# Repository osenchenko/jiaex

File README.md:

#  JiaEX - split keyboard for extended alphabets.

`assembled-keyboard.stl` - 3d model of assembled keyboard.

## Features

- enough keys for placing on base layer all letters for extended alphabets (alphabets with more than 26 letters).
- plenty of keys for playing with different variants to find your best setup.
- one keyboard for all operating systems. Switch between settings for different operating systems with a shortcut (currently settings for Linux and Windows are implemented).
- used AT90USB1286 with 128 KB memory. No limits for storing settings.
- wide choice of keycaps. The keyboard is designed for maximum use of keycap sets from standard keyboards. 1.75U keys of thumb cluster and 1.5U vertical keys can be replaced with 1.5U or 1.25U keys in any combination.
- wrist pad is rigidly attached to the keyboard. The keyboard is not intended to be used without a wrist pad.
- the display shows current default layout (for example Linux) and current active layer plus Caps Lock state.
- powered by QMK.

## Layout

[keyboard-layout-editor.com](http://www.keyboard-layout-editor.com/#/gists/80bbde035c246cb868fec8fd4ef6ad40)

## Build guide

### Folders

- `case` - stl-files for 3d printing case and wrist pads. <br/>Case and wrist pads are designed by Alexander_St enginemojo@gmail.com.
- `datasheets` - datasheets for some used parts
- `firmware` - source files for QMK firmware
- `pcb` - KiCAD source and gerber files for manufacturing PCB.
- `plate` - dxf for laser cutting metal plate.

### Firmware

- install qmk 
- copy folder `jiaex` from `firmware` to `keyboards` folder of qmk installation
- <u>Until pull request [#11487](https://github.com/qmk/qmk_firmware/pull/11487) is not merged in QMK master you must apply this pull request by yourself.</u>
- run `qmk flash -kb jiaex -km default` 

### PCB and Case

Kicad libraries used:

- https://github.com/XenGi/teensy_library

### Bill of materials

| Name                                          | Value                                                                                                            | Quantity |
| --------------------------------------------- | ---------------------------------------------------------------------------------------------------------------- | -------: |
| Microcontroller board                         | [Teensy ++ 2.0](https://www.pjrc.com/store/teensypp.html)                                                        |        2 |
| SMD Diode                                     | 1N4148 [SOD-123]                                                                                                 |       68 |
| SMD Resistor 1206                             | 30K                                                                                                              |        2 |
| SMD Resistor 1206                             | 3K                                                                                                               |        4 |
| SMD Resistor 1206                             | 10K                                                                                                              |        1 |
| Jack RJ-22                                    | [215875-1, Conn RJ-22 F 4 POS 1.02mm Solder RA Thru-Hole 4 Terminal 1 Port Cat 3 T/R](datasheets/Jack_RJ-22.pdf) |        2 |
| OLED display                                  | [0.91 inch OLED Module 128x32, I2C](datasheets/OLED_Module_User_Manual_EN.pdf)                                   |        1 |
| Plug for OLED display                         | [PLS-4R (DS1022-1x4R)](datasheets/DS1022.pdf)                                                                    |        1 |
| Key switch                                    | Any Cherry MX compatible                                                                                         |       68 |
| Key stabilyzers                               | Any Cherry MX compatible, plate mount                                                                            |        6 |
| 4-wire phone cable with RJ11 (TP-4P4C) jacks. | Max length of cable - 11 cm.                                                                                     |        1 |
| Rubber feet                                   | At your own choice. I use [RF-3004](datasheets/DOC004505728.pdf)                                                 |      --- |
| Metal plate. Thickness                        | 1.5 mm                                                                                                           |        2 |

### Screws

| Name                                                                                                   | Diameter, mm | Length, mm | Image               | Quantity | Notes                                                   |
| ------------------------------------------------------------------------------------------------------ | -----------: | ---------: | ------------------- | -------: | ------------------------------------------------------- |
| Self-tapping screw for plastic, countersunk head, blunt end, Phillips head, full thread, ART 9090      |            3 |      8..10 |  |       20 | Drill the hole with a 2 mm drill before insert screw.   |
| Self-tapping screw DIN 7981 FH (A2) with a blunt end with a half-cylindrical head, head Phillips ST2.2 |          2.2 |     6.5..8 |  |        8 | Drill the hole with a 1.2 mm drill before insert screw. |

## Inspiration

Keyboard is inspired by the following keyboards:

- Jian
- Jiran
- Ultimate Hacking Keyboard
- Ergodox

Layout inspired by ideas of:

- Tonsky https://tonsky.livejournal.com/318571.html (for non-Russian speakers use google translate  in Chrome browser)
- Ultimate Hacking Keyboard
- Optozorax https://github.com/optozorax/moonlander (for non-Russian speakers use google translate in Chrome browser)

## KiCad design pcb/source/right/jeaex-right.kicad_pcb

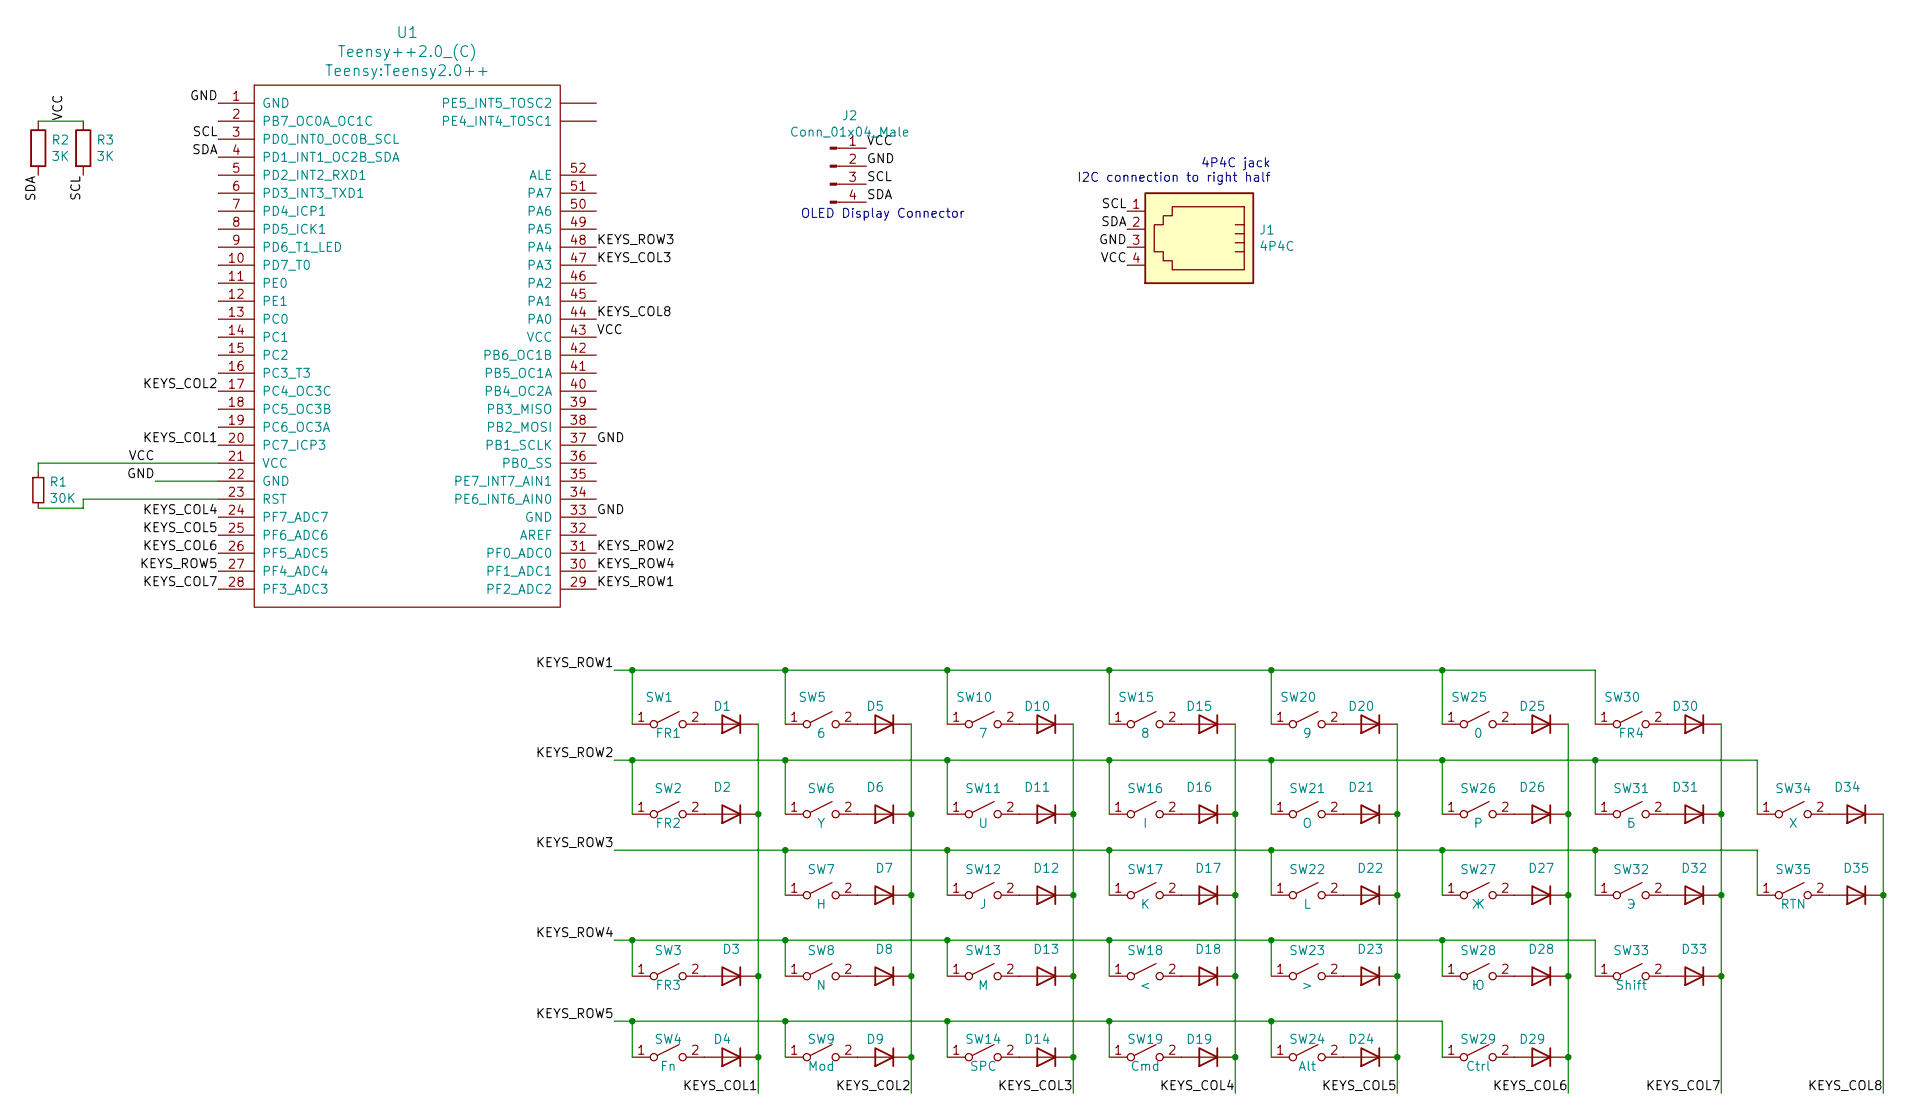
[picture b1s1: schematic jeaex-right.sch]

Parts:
D1, D2, D3, D4, D5, D6, D7, D8, D9, D10, D11, D12, D13, D14, D15, D16, D17, D18, D19, D20, D21, D22, D23, D24, D25, D26, D27, D28, D29, D30, D31, D32, D33, D34, D35: 1N4148W; D_SOD-123
J1: 4P4C; 4P4C_Jack_0955012441
J2: Conn_01x04_Male; PinHeader_1x04_P2.54mm_Vertical
R1: 30K; R_1206_3216Metric_Pad1.30x1.75mm_HandSolder
R2, R3: 3K; R_1206_3216Metric_Pad1.30x1.75mm_HandSolder
SW1: FR1; SW_Cherry_MX_1.00u_Plate
SW2: FR2; SW_Cherry_MX_1.50u_Plate
SW3: FR3; SW_Cherry_MX_1.50u_Plate
SW4: Fn; SW_Cherry_MX_1.75u_Plate
SW5: 6; SW_Cherry_MX_1.00u_Plate
SW6: Y; SW_Cherry_MX_1.00u_Plate
SW7: H; SW_Cherry_MX_1.00u_Plate
SW8: N; SW_Cherry_MX_1.00u_Plate
SW9: Mod; SW_Cherry_MX_1.75u_Plate
SW10: 7; SW_Cherry_MX_1.00u_Plate
SW11: U; SW_Cherry_MX_1.00u_Plate
SW12: J; SW_Cherry_MX_1.00u_Plate
SW13: M; SW_Cherry_MX_1.00u_Plate
SW14: SPC; SW_Cherry_MX_1.75u_Plate
SW15: 8; SW_Cherry_MX_1.00u_Plate
SW16: I; SW_Cherry_MX_1.00u_Plate
SW17: K; SW_Cherry_MX_1.00u_Plate
SW18: <; SW_Cherry_MX_1.00u_Plate
SW19: Cmd; SW_Cherry_MX_1.25u_Plate
SW20: 9; SW_Cherry_MX_1.00u_Plate
SW21: O; SW_Cherry_MX_1.00u_Plate
SW22: L; SW_Cherry_MX_1.00u_Plate
SW23: >; SW_Cherry_MX_1.00u_Plate
SW24: Alt; SW_Cherry_MX_1.25u_Plate
SW25: 0; SW_Cherry_MX_1.00u_Plate
SW26: P; SW_Cherry_MX_1.00u_Plate
SW27: Ж; SW_Cherry_MX_1.00u_Plate
SW28: Ю; SW_Cherry_MX_1.00u_Plate
SW29: Ctrl; SW_Cherry_MX_2.25u_Plate
SW30: FR4; SW_Cherry_MX_2.00u_Plate
SW31: Б; SW_Cherry_MX_1.00u_Plate
SW32: Э; SW_Cherry_MX_1.00u_Plate
SW33: Shift; SW_Cherry_MX_2.75u_Plate
SW34: Х; SW_Cherry_MX_1.00u_Plate
SW35: RTN; SW_Cherry_MX_2.25u_Plate
U1: Teensy++2.0_(C); Teensy2.0++

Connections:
/GND: J1.3, J2.2, U1.1 (GND), U1.22 (GND), U1.33 (GND), U1.37 (PB1_SCLK)
/KEYS_COL1: D1.1 (K), D2.1 (K), D3.1 (K), D4.1 (K), U1.20 (PC7_ICP3)
/KEYS_COL2: D5.1 (K), D6.1 (K), D7.1 (K), D8.1 (K), D9.1 (K), U1.17 (PC4_OC3C)
/KEYS_COL3: D10.1 (K), D11.1 (K), D12.1 (K), D13.1 (K), D14.1 (K), U1.47 (PA3)
/KEYS_COL4: D15.1 (K), D16.1 (K), D17.1 (K), D18.1 (K), D19.1 (K), U1.24 (PF7_ADC7)
/KEYS_COL5: D20.1 (K), D21.1 (K), D22.1 (K), D23.1 (K), D24.1 (K), U1.25 (PF6_ADC6)
/KEYS_COL6: D25.1 (K), D26.1 (K), D27.1 (K), D28.1 (K), D29.1 (K), U1.26 (PF5_ADC5)
/KEYS_COL7: D30.1 (K), D31.1 (K), D32.1 (K), D33.1 (K), U1.28 (PF3_ADC3)
/KEYS_COL8: D34.1 (K), D35.1 (K), U1.44 (PA0)
/KEYS_ROW1: SW1.1 (A), SW5.1 (A), SW10.1 (A), SW15.1 (A), SW20.1 (A), SW25.1 (A), SW30.1 (A), U1.29 (PF2_ADC2)
/KEYS_ROW2: SW2.1 (A), SW6.1 (A), SW11.1 (A), SW16.1 (A), SW21.1 (A), SW26.1 (A), SW31.1 (A), SW34.1 (A), U1.31 (PF0_ADC0)
/KEYS_ROW3: SW7.1 (A), SW12.1 (A), SW17.1 (A), SW22.1 (A), SW27.1 (A), SW32.1 (A), SW35.1 (A), U1.48 (PA4)
/KEYS_ROW4: SW3.1 (A), SW8.1 (A), SW13.1 (A), SW18.1 (A), SW23.1 (A), SW28.1 (A), SW33.1 (A), U1.30 (PF1_ADC1)
/KEYS_ROW5: SW4.1 (A), SW9.1 (A), SW14.1 (A), SW19.1 (A), SW24.1 (A), SW29.1 (A), U1.27 (PF4_ADC4)
/SCL: J1.1, J2.3, R3.2, U1.3 (PD0_INT0_OC0B_SCL)
/SDA: J1.2, J2.4, R2.2, U1.4 (PD1_INT1_OC2B_SDA)
/VCC: J1.4, J2.1, R1.1, R2.1, R3.1, U1.21 (VCC), U1.43 (VCC)
unnamed: D1.2 (A), SW1.2 (B)
unnamed: D2.2 (A), SW2.2 (B)
unnamed: D3.2 (A), SW3.2 (B)
unnamed: D4.2 (A), SW4.2 (B)
unnamed: D5.2 (A), SW5.2 (B)
unnamed: D6.2 (A), SW6.2 (B)
unnamed: D7.2 (A), SW7.2 (B)
unnamed: D8.2 (A), SW8.2 (B)
unnamed: D9.2 (A), SW9.2 (B)
unnamed: D10.2 (A), SW10.2 (B)
unnamed: D11.2 (A), SW11.2 (B)
unnamed: D12.2 (A), SW12.2 (B)
unnamed: D13.2 (A), SW13.2 (B)
unnamed: D14.2 (A), SW14.2 (B)
unnamed: D15.2 (A), SW15.2 (B)
unnamed: D16.2 (A), SW16.2 (B)
unnamed: D17.2 (A), SW17.2 (B)
unnamed: D18.2 (A), SW18.2 (B)
unnamed: D19.2 (A), SW19.2 (B)
unnamed: D20.2 (A), SW20.2 (B)
unnamed: D21.2 (A), SW21.2 (B)
unnamed: D22.2 (A), SW22.2 (B)
unnamed: D23.2 (A), SW23.2 (B)
unnamed: D24.2 (A), SW24.2 (B)
unnamed: D25.2 (A), SW25.2 (B)
unnamed: D26.2 (A), SW26.2 (B)
unnamed: D27.2 (A), SW27.2 (B)
unnamed: D28.2 (A), SW28.2 (B)
unnamed: D29.2 (A), SW29.2 (B)
unnamed: D30.2 (A), SW30.2 (B)
unnamed: D31.2 (A), SW31.2 (B)
unnamed: D32.2 (A), SW32.2 (B)
unnamed: D33.2 (A), SW33.2 (B)
unnamed: D34.2 (A), SW34.2 (B)
unnamed: D35.2 (A), SW35.2 (B)
unnamed: R1.2, U1.23 (RST)

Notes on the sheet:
4P4C jack I2C connection to right half
OLED Display Connector

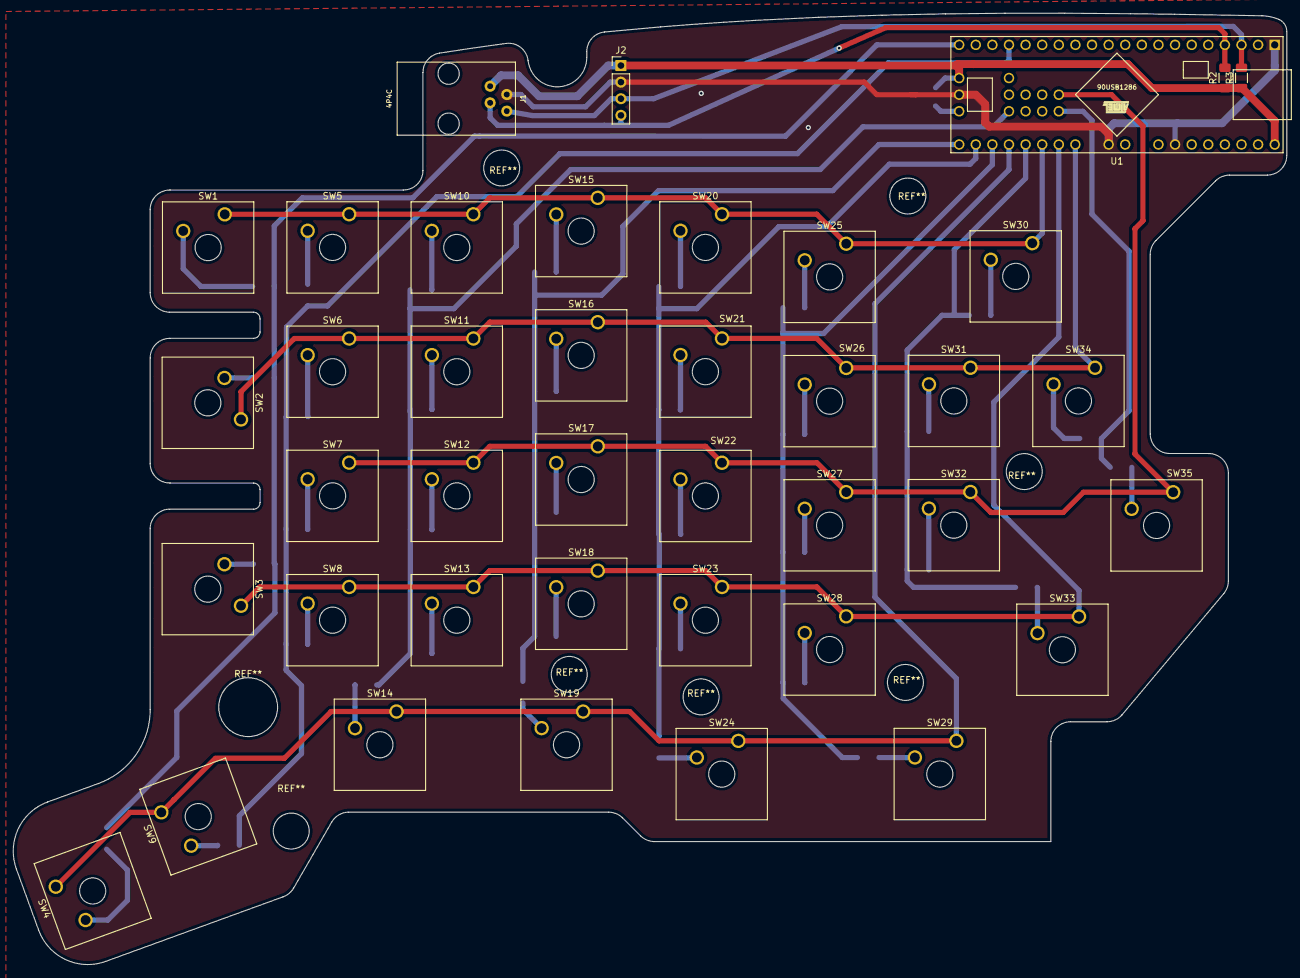
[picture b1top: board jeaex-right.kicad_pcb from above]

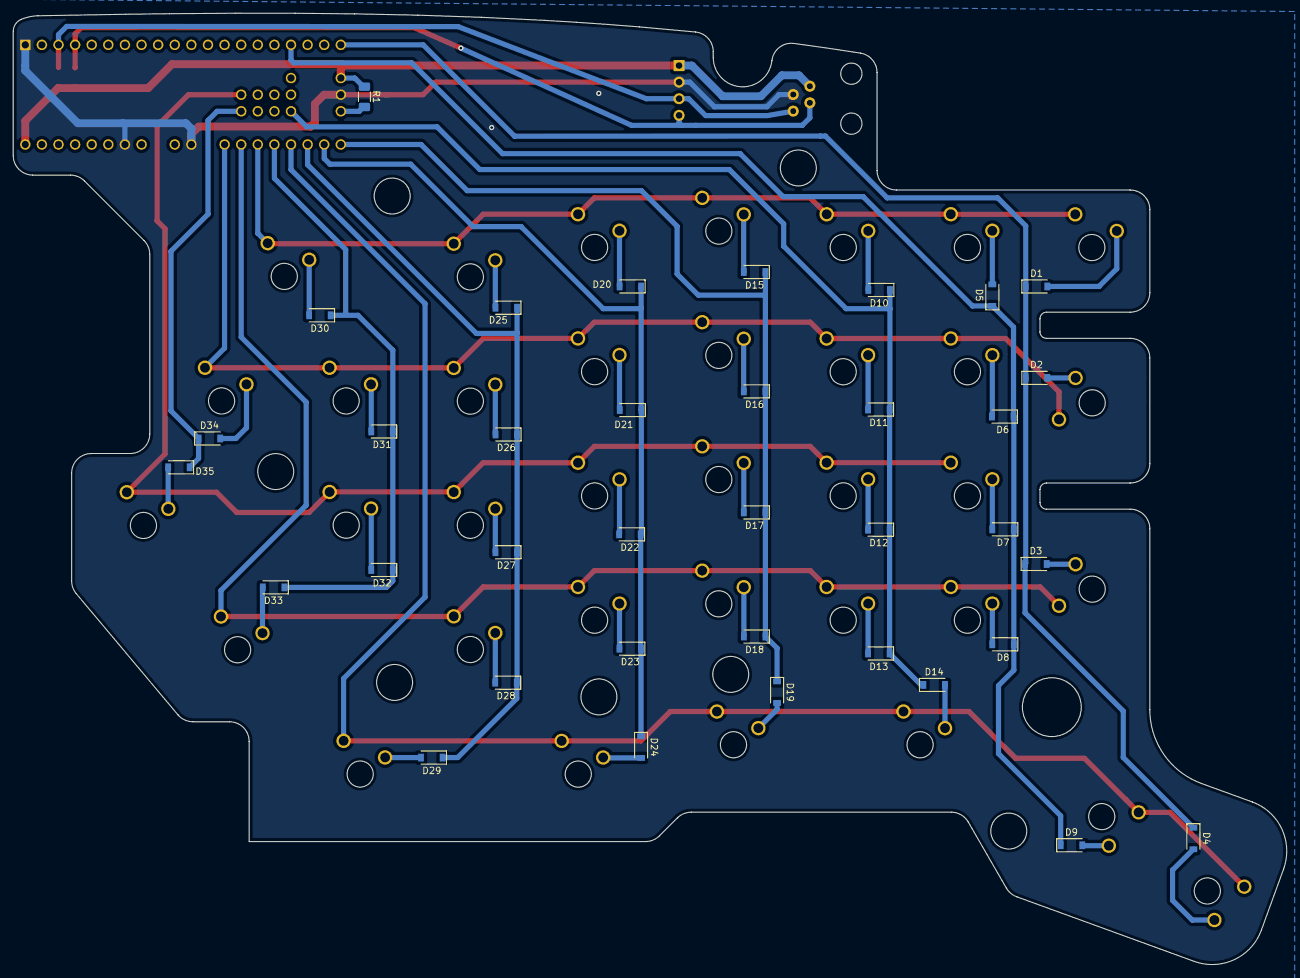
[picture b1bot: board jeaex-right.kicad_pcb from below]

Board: 2 copper layers, 194.8 x 145.5 mm, 76 parts (36 on the bottom side), 53 nets.

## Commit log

2021-01-19 Update README. Change filenames of datasheet files
2021-01-19 move source files to jiaex folder
